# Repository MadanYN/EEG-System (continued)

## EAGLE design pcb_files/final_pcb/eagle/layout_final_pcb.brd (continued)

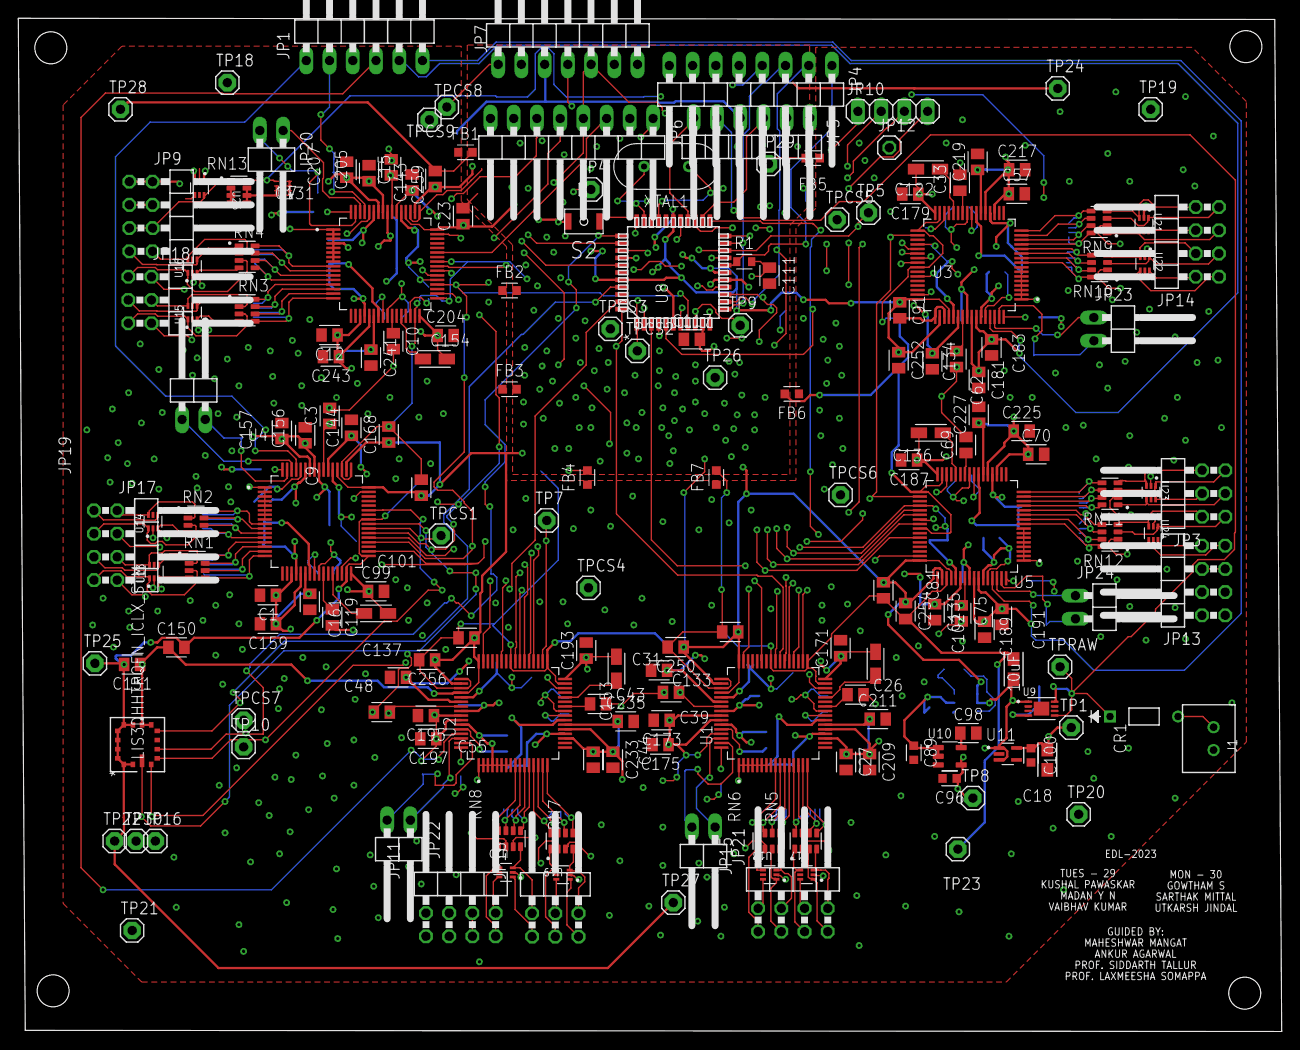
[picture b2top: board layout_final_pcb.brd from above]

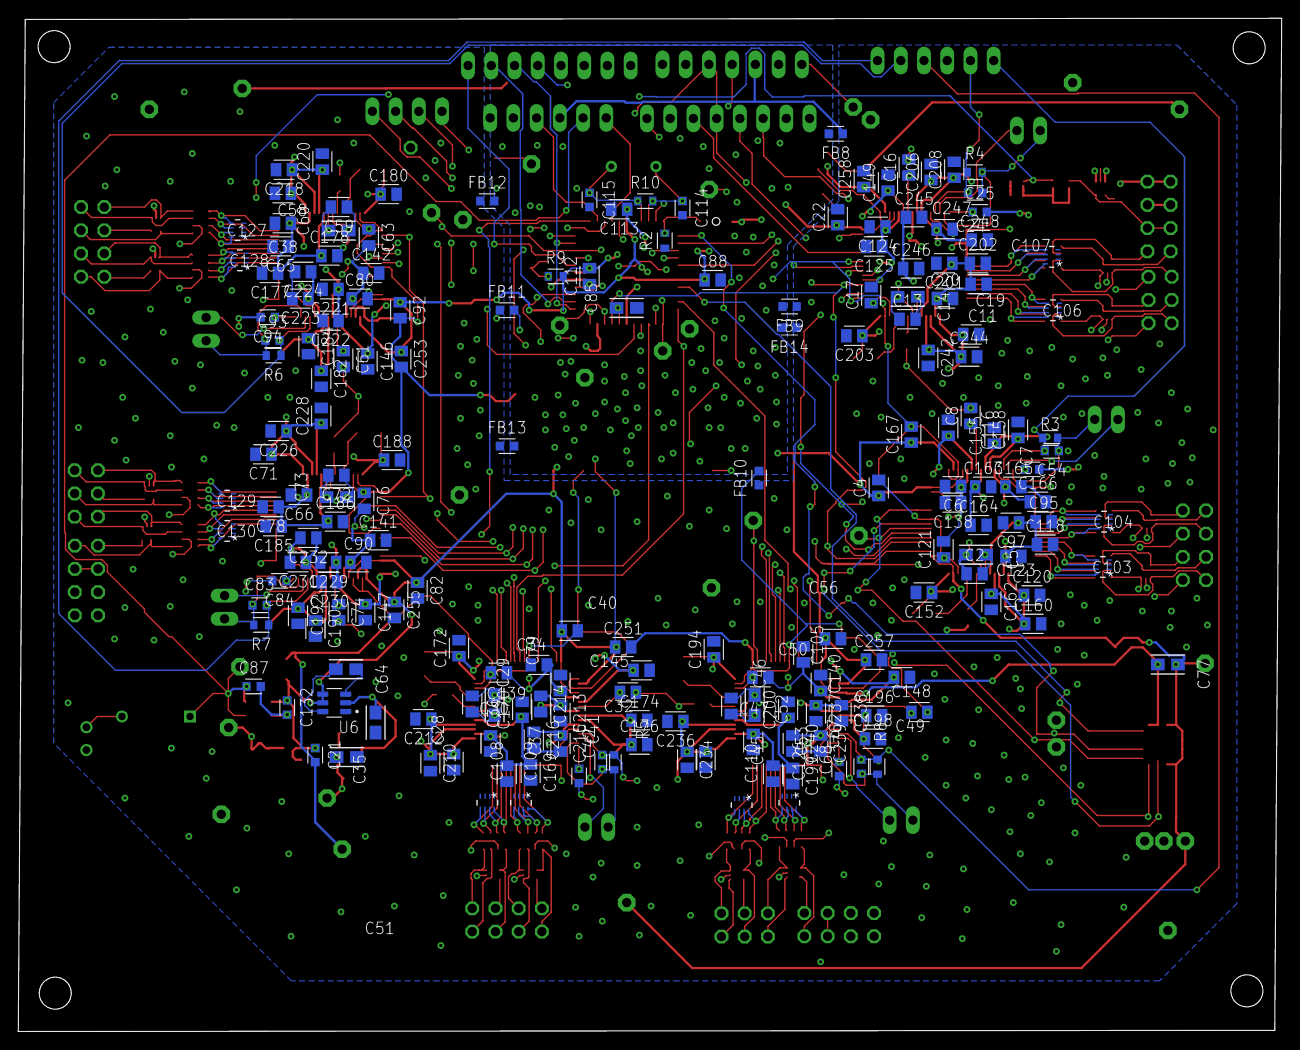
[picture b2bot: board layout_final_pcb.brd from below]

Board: 4 copper layers, 138.2 x 110.8 mm, 377 parts (192 on the bottom side), 200 nets.

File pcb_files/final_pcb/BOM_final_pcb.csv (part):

"Part";"Value";"Device";"Package";"Description";"CATEGORY";"COPYRIGHT";"DESCRIPTION";"FILTER_TYPE";"FREQUENCY";"IMPEDANCE_FREQ";"MANUFACTURER";"MANUFACTURER_PART_NUMBER";"MFR_NAME";"MPN";"OPERATING_TEMP";"OPERATING_TEMPERATURE";"PACKAGE";"PART_STATUS";"RATING";"REVERSE_VOLTAGE";"ROHS_COMPLIANCE";"ROHS_COMPLIANT";"SERIES";"STANDARD";"SUB-CATEGORY";"SUBCATEGORY";"SUB_CATEGORY";"THERMALLOSS";"THERMAL_LOSS";"TOLERANCE";"TYPE";"VALUE";"VOLTAGE_RATING";
"C1";"0.1uF";"C_CHIP-0805(2012-METRIC)";"CAPC2012X110";"Capacitor - Generic";"Capacitor";"";"";"";"";"";"";"";"";"";"";"";"";"";"";"";"";"";"";"";"";"";"";"";"";"";"";"";"";
"C2";"0.1uF";"C_CHIP-0805(2012-METRIC)";"CAPC2012X110";"Capacitor - Generic";"Capacitor";"";"";"";"";"";"";"";"";"";"";"";"";"";"";"";"";"";"";"";"";"";"";"";"";"";"";"";"";
"C3";"1uF";"C_CHIP-0805(2012-METRIC)";"CAPC2012X110";"Capacitor - Generic";"Capacitor";"";"";"";"";"";"";"";"";"";"";"";"";"";"";"";"";"";"";"";"";"";"";"";"";"";"";"";"";
"C4";"1uF";"C_CHIP-0805(2012-METRIC)";"CAPC2012X110";"Capacitor - Generic";"Capacitor";"";"";"";"";"";"";"";"";"";"";"";"";"";"";"";"";"";"";"";"";"";"";"";"";"";"";"";"";
"C5";"10uF ";"293D106X0016A2TE3CAP_293D-A_VSS";"CAP_293D-A_VSS";"";"";"Copyright (C) 2023 Ultra Librarian. All rights reserved.";"";"";"";"";"";"293D106X0016A2TE3";"Vishay";"";"";"";"";"";"";"";"";"";"";"";"";"";"";"";"";"";"";"";"";
"C6";"0.1uF";"C_CHIP-0805(2012-METRIC)";"CAPC2012X110";"Capacitor - Generic";"Capacitor";"";"";"";"";"";"";"";"";"";"";"";"";"";"";"";"";"";"";"";"";"";"";"";"";"";"";"";"";
"C7";"100pF";"C_CHIP-0603(1608-METRIC)";"CAPC1608X85";"Capacitor - Generic";"Capacitor";"";"";"";"";"";"";"";"";"";"";"";"";"";"";"";"";"";"";"";"";"";"";"";"";"";"";"";"";
"C8";"0.1uF";"C_CHIP-0805(2012-METRIC)";"CAPC2012X110";"Capacitor - Generic";"Capacitor";"";"";"";"";"";"";"";"";"";"";"";"";"";"";"";"";"";"";"";"";"";"";"";"";"";"";"";"";
"C9";"0.1uF";"C_CHIP-0805(2012-METRIC)";"CAPC2012X110";"Capacitor - Generic";"Capacitor";"";"";"";"";"";"";"";"";"";"";"";"";"";"";"";"";"";"";"";"";"";"";"";"";"";"";"";"";
"C10";"1uF";"C_CHIP-0805(2012-METRIC)";"CAPC2012X110";"Capacitor - Generic";"Capacitor";"";"";"";"";"";"";"";"";"";"";"";"";"";"";"";"";"";"";"";"";"";"";"";"";"";"";"";"";
"C11";"0.1uF";"C_CHIP-0805(2012-METRIC)";"CAPC2012X110";"Capacitor - Generic";"Capacitor";"";"";"";"";"";"";"";"";"";"";"";"";"";"";"";"";"";"";"";"";"";"";"";"";"";"";"";"";
"C12";"1uF";"C_CHIP-0805(2012-METRIC)";"CAPC2012X110";"Capacitor - Generic";"Capacitor";"";"";"";"";"";"";"";"";"";"";"";"";"";"";"";"";"";"";"";"";"";"";"";"";"";"";"";"";
"C13";"0.1uF";"C_CHIP-0805(2012-METRIC)";"CAPC2012X110";"Capacitor - Generic";"Capacitor";"";"";"";"";"";"";"";"";"";"";"";"";"";"";"";"";"";"";"";"";"";"";"";"";"";"";"";"";
"C14";"10uF ";"293D106X0016A2TE3CAP_293D-A_VSS";"CAP_293D-A_VSS";"";"";"Copyright (C) 2023 Ultra Librarian. All rights reserved.";"";"";"";"";"";"293D106X0016A2TE3";"Vishay";"";"";"";"";"";"";"";"";"";"";"";"";"";"";"";"";"";"";"";"";
"C15";"1uF";"C_CHIP-0805(2012-METRIC)";"CAPC2012X110";"Capacitor - Generic";"Capacitor";"";"";"";"";"";"";"";"";"";"";"";"";"";"";"";"";"";"";"";"";"";"";"";"";"";"";"";"";
"C16";"0.1uF";"C_CHIP-0805(2012-METRIC)";"CAPC2012X110";"Capacitor - Generic";"Capacitor";"";"";"";"";"";"";"";"";"";"";"";"";"";"";"";"";"";"";"";"";"";"";"";"";"";"";"";"";
"C17";"1uF";"C_CHIP-0805(2012-METRIC)";"CAPC2012X110";"Capacitor - Generic";"Capacitor";"";"";"";"";"";"";"";"";"";"";"";"";"";"";"";"";"";"";"";"";"";"";"";"";"";"";"";"";
"C18";"10uF ";"293D106X0016A2TE3CAP_293D-A_VSS";"CAP_293D-A_VSS";"";"";"Copyright (C) 2023 Ultra Librarian. All rights reserved.";"";"";"";"";"";"293D106X0016A2TE3";"Vishay";"";"";"";"";"";"";"";"";"";"";"";"";"";"";"";"";"";"";"";"";
"C19";"1uF";"C_CHIP-0805(2012-METRIC)";"CAPC2012X110";"Capacitor - Generic";"Capacitor";"";"";"";"";"";"";"";"";"";"";"";"";"";"";"";"";"";"";"";"";"";"";"";"";"";"";"";"";
"C20";"0.1uF";"C_CHIP-0805(2012-METRIC)";"CAPC2012X110";"Capacitor - Generic";"Capacitor";"";"";"";"";"";"";"";"";"";"";"";"";"";"";"";"";"";"";"";"";"";"";"";"";"";"";"";"";
"C21";"2.2uF";"C_CHIP-0603(1608-METRIC)";"CAPC1608X85";"Capacitor - Generic";"Capacitor";"";"";"";"";"";"";"";"";"";"";"";"";"";"";"";"";"";"";"";"";"";"";"";"";"";"";"";"";
"C22";"1uF";"C_CHIP-0805(2012-METRIC)";"CAPC2012X110";"Capacitor - Generic";"Capacitor";"";"";"";"";"";"";"";"";"";"";"";"";"";"";"";"";"";"";"";"";"";"";"";"";"";"";"";"";
"C23";"0.1uF";"C_CHIP-0805(2012-METRIC)";"CAPC2012X110";"Capacitor - Generic";"Capacitor";"";"";"";"";"";"";"";"";"";"";"";"";"";"";"";"";"";"";"";"";"";"";"";"";"";"";"";"";
"C24";"1.5nF";"C_CHIP-0603(1608-METRIC)";"CAPC1608X85";"Capacitor - Generic";"Capacitor";"";"";"";"";"";"";"";"";"";"";"";"";"";"";"";"";"";"";"";"";"";"";"";"";"";"";"";"";
"C25";"100pF";"C_CHIP-0603(1608-METRIC)";"CAPC1608X85";"Capacitor - Generic";"Capacitor";"";"";"";"";"";"";"";"";"";"";"";"";"";"";"";"";"";"";"";"";"";"";"";"";"";"";"";"";
"C26";"1uF";"C_CHIP-0805(2012-METRIC)";"CAPC2012X110";"Capacitor - Generic";"Capacitor";"";"";"";"";"";"";"";"";"";"";"";"";"";"";"";"";"";"";"";"";"";"";"";"";"";"";"";"";
"C27";"0.1uF";"C_CHIP-0805(2012-METRIC)";"CAPC2012X110";"Capacitor - Generic";"Capacitor";"";"";"";"";"";"";"";"";"";"";"";"";"";"";"";"";"";"";"";"";"";"";"";"";"";"";"";"";
"C28";"1uF";"C_CHIP-0805(2012-METRIC)";"CAPC2012X110";"Capacitor - Generic";"Capacitor";"";"";"";"";"";"";"";"";"";"";"";"";"";"";"";"";"";"";"";"";"";"";"";"";"";"";"";"";
"C29";"0.1uF";"C_CHIP-0805(2012-METRIC)";"CAPC2012X110";"Capacitor - Generic";"Capacitor";"";"";"";"";"";"";"";"";"";"";"";"";"";"";"";"";"";"";"";"";"";"";"";"";"";"";"";"";
"C30";"10uF ";"293D106X0016A2TE3CAP_293D-A_VSS";"CAP_293D-A_VSS";"";"";"Copyright (C) 2023 Ultra Librarian. All rights reserved.";"";"";"";"";"";"293D106X0016A2TE3";"Vishay";"";"";"";"";"";"";"";"";"";"";"";"";"";"";"";"";"";"";"";"";
"C31";"1uF";"C_CHIP-0805(2012-METRIC)";"CAPC2012X110";"Capacitor - Generic";"Capacitor";"";"";"";"";"";"";"";"";"";"";"";"";"";"";"";"";"";"";"";"";"";"";"";"";"";"";"";"";
"C32";"0.1uF";"C_CHIP-0805(2012-METRIC)";"CAPC2012X110";"Capacitor - Generic";"Capacitor";"";"";"";"";"";"";"";"";"";"";"";"";"";"";"";"";"";"";"";"";"";"";"";"";"";"";"";"";
"C33";"1uF";"C_CHIP-0805(2012-METRIC)";"CAPC2012X110";"Capacitor - Generic";"Capacitor";"";"";"";"";"";"";"";"";"";"";"";"";"";"";"";"";"";"";"";"";"";"";"";"";"";"";"";"";
"C34";"1uF";"C_CHIP-0805(2012-METRIC)";"CAPC2012X110";"Capacitor - Generic";"Capacitor";"";"";"";"";"";"";"";"";"";"";"";"";"";"";"";"";"";"";"";"";"";"";"";"";"";"";"";"";
"C35";"10uF ";"293D106X0016A2TE3CAP_293D-A_VSS";"CAP_293D-A_VSS";"";"";"Copyright (C) 2023 Ultra Librarian. All rights reserved.";"";"";"";"";"";"293D106X0016A2TE3";"Vishay";"";"";"";"";"";"";"";"";"";"";"";"";"";"";"";"";"";"";"";"";
"C36";"1uF";"C_CHIP-0805(2012-METRIC)";"CAPC2012X110";"Capacitor - Generic";"Capacitor";"";"";"";"";"";"";"";"";"";"";"";"";"";"";"";"";"";"";"";"";"";"";"";"";"";"";"";"";
"C37";"0.1uF";"C_CHIP-0805(2012-METRIC)";"CAPC2012X110";"Capacitor - Generic";"Capacitor";"";"";"";"";"";"";"";"";"";"";"";"";"";"";"";"";"";"";"";"";"";"";"";"";"";"";"";"";
"C38";"1uF";"C_CHIP-0805(2012-METRIC)";"CAPC2012X110";"Capacitor - Generic";"Capacitor";"";"";"";"";"";"";"";"";"";"";"";"";"";"";"";"";"";"";"";"";"";"";"";"";"";"";"";"";
"C39";"1uF";"C_CHIP-0805(2012-METRIC)";"CAPC2012X110";"Capacitor - Generic";"Capacitor";"";"";"";"";"";"";"";"";"";"";"";"";"";"";"";"";"";"";"";"";"";"";"";"";"";"";"";"";
"C40";"0.1uF";"C_CHIP-0805(2012-METRIC)";"CAPC2012X110";"Capacitor - Generic";"Capacitor";"";"";"";"";"";"";"";"";"";"";"";"";"";"";"";"";"";"";"";"";"";"";"";"";"";"";"";"";
"C41";"1.5nF";"C_CHIP-0603(1608-METRIC)";"CAPC1608X85";"Capacitor - Generic";"Capacitor";"";"";"";"";"";"";"";"";"";"";"";"";"";"";"";"";"";"";"";"";"";"";"";"";"";"";"";"";
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
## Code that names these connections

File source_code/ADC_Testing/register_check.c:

/*	EE344 - Electronic Design Lab
	Groups: TUES-29 and MON-30
	Project: EEG Acquisition System
  
	This code is for initial testing of ADS1194 using PIC32MX clicker board
	IDE used - NECTO Studio v3.0.0
	
	Clock mode: internal

	Supply from clicker board:
	DVDD - 3.3V
	AVDD - 5V "CAUTION: Supply voltages higher than 5.25V can permanently damage the ADC"
	
	SPI Module (clicker):
	CS - pin RG9
	SCLK - pin RG6
	MOSI - pin RG8
	MISO - pin RG7
	RESET - pin RD7
	DRDY(INT) - pin RD11
	
	UART Module (clicker):
	Tx - pin RB14
	Rx - pin RB8
*/


// There are 26 registers
#define no_regs 26

// Defining the pin mappings
sbit cs at RG9_bit;			// chip select' pin
sbit sclk at RG6_bit;		// serial clock pin
sbit dout at RG8_bit;		// uC's data_out, i.e. MOSI pin
sbit din at RG7_bit;		// uC's data_in, i.e. MISO pin
sbit txd at RB14_bit;		// TX pin for UART
sbit rxd at RB8_bit;			// RX pin for UART
sbit reset at RD7_bit;		// RESET' pin
sbit drdy at RD11_bit;		// DRDY' (INT) pin

// Defining the input/output direction variables
sbit cs_direction at TRISG9_bit;
sbit sclk_direction at TRISG6_bit;
sbit dout_direction at TRISG8_bit;
sbit din_direction at TRISG7_bit;
sbit tx_direction at TRISB14_bit;
sbit rx_direction at TRISB8_bit;
sbit reset_direction at TRISD7_bit;
sbit drdy_direction at TRISD11_bit;

// Creating array of registers
char reg[no_regs];


void init(){
	cs_direction = 0;		// set CS' pin as output
	sclk_direction = 0;		// set SCLK pin as output
	dout_direction = 0;		// set MOSI pin as output
	din_direction = 1;		// set MISO pin as input
	tx_direction = 0;		// set TX pin as output
	rx_direction = 1;		// set RX pin as input
	reset_direction = 0;	// set RESET' pin as output
	drdy_direction = 0;		// set DRDY' pin as output

	cs = 1;					// deselect ADC (active low)

	reset = 0;			// reset the ADC (active low)
	Delay_ms(10);		// 10 ms delay
	reset = 1;
	Delay_ms(10);

	SPI2_Init_Advanced(_SPI_MASTER, _SPI_16_BIT, 80, _SPI_SS_DISABLE, _SPI_DATA_SAMPLE_MIDDLE, _SPI_CLK_IDLE_LOW, _SPI_IDLE_2_ACTIVE);		// Initialize SPI Module (Fosc/80 = 1MHz)
	UART5_Init(9600);		// baud rate = 9600
}


int main(){
	
	init();

	cs = 0;				// select ADC (active low)

	SPI2_Write(0x06);	// reset command
	Delay_us(18);		// 18 microsecond delay (18 SCLK cycles required)
	SPI2_Write(0x08);	// start command (to start conversions)
	Delay_us(4);		// 4 SCLK cycles
	SPI2_Write(0x11);	// stop read data continuously mode
	Delay_us(4);		// 4 SCLK cycles		

	Delay_us(8);

	// Set GPIO pins as output
	SPI2_Write(0x4E);	// WREG command 1st opcode byte for GPIO register
	Delay_us(8);		// 8 SCLK cycles
	SPI2_Write(0x00);	// WREG command 2nd opcode byte for GPIO register
	Delay_us(8);
	SPI2_Write(0x00);	// lower nibble sets the 4 GPIO pins as output and upper nibble sets their values to 0

	Delay_us(8);

	UART5_Write_Text("Reading Registers\n");
	SPI2_Write(0x20);			// RREG command 1st opcode byte
	Delay_us(8);				// 8 SCLK cycles required
	SPI2_Write(0x19);			// RREG command 2nd opcode byte
	Delay_us(8);

	int i = 0;
	while(i<26){
		reg[i] = SPI2_Read(0);	// reading register data
		Delay_us(8);			// 8 SCLK cycles
		i++;
	}

	i = 0;
	while(i<26){
		char temp1 = reg[i] & 0x0F;		// separating the nibbles to see data in hex format (lower nibble here)
		char temp2 = reg[i] >> 4;		// upper nibble
		UART5_Write(temp2 + 48);		// ASCII value of 0 is 48
		UART5_Write(temp1 + 48);
		UART5_Write_Text("\n");
		i++;
	}

	while(1){

	}
	
	return 0;
}
